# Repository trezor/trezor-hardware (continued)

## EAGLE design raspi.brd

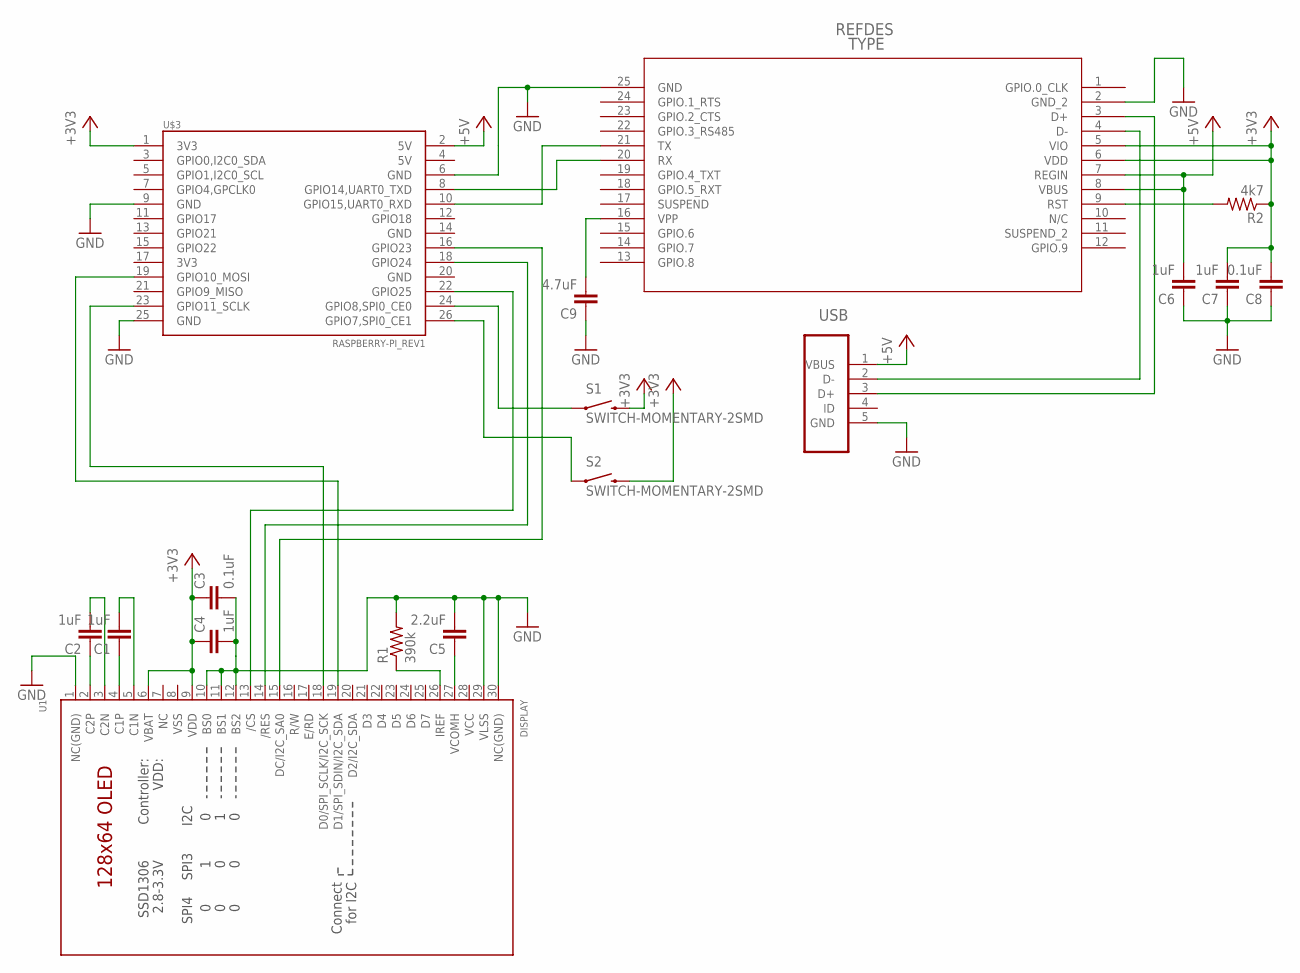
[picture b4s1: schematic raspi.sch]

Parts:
C1, C2, C4, C6, C7: 1uF; 0805
C3, C8: 0.1uF; 0805
C5: 2.2uF; 0805
C9: 4.7uF; 0805
R1: 390k; 0805
R2: 4k7; 0805
S1, S2: SWITCH-MOMENTARY-2SMD; TACTILE_SWITCH_SMD
U1: DISPLAY; UG-2864HSWEG01_0.96IN_WRAPAROUND
U2: CP2110-F01-GM
U$3: RASPBERRY-PI_REV1
USB: 47346-0001; MOLEX_47346-0001

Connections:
+3V3: C3.1, C4.1, C7.2, C8.2, R2.1, S1.3 (2), S2.3 (2), U1.6 (VBAT), U1.9 (VDD), U2.5 (VIO), U2.6 (VDD), U$3.1 (3V3)
+5V: C6.2, U2.7 (REGIN), U2.8 (VBUS), U$3.2 (5V), USB.1 (VBUS)
GND: C3.2, C4.2, C5.2, C6.1, C7.1, C8.1, C9.1, R1.2, U1.1 (NC(GND)), U1.10 (BS0), U1.11 (BS1), U1.12 (BS2), U1.29 (VLSS), U1.30 (NC(GND)), U2.2 (GND_2), U2.25 (GND), U$3.6 (GND), U$3.9 (GND), U$3.25 (GND), USB.5 (GND)
unnamed: U1.19 (D1/SPI_SDIN/I2C_SDA), U$3.19 (GPIO10_MOSI)
unnamed: S2.1, U$3.26 (GPIO7,SPI0_CE1)
unnamed: S1.1, U$3.24 (GPIO8,SPI0_CE0)
unnamed: U1.15 (DC/I2C_SA0), U$3.16 (GPIO23)
unnamed: U1.18 (D0/SPI_SCLK/I2C_SCK), U$3.23 (GPIO11_SCLK)
unnamed: C5.1, U1.27 (VCOMH)
unnamed: U1.13 (/CS), U$3.22 (GPIO25)
unnamed: U1.14 (/RES), U$3.18 (GPIO24)
unnamed: R1.1, U1.26 (IREF)
unnamed: C2.1, U1.2 (C2P)
unnamed: C1.1, U1.4 (C1P)
unnamed: C2.2, U1.3 (C2N)
unnamed: C1.2, U1.5 (C1N)
unnamed: C9.2, U2.16 (VPP)
unnamed: U2.21 (TX), U$3.10 (GPIO15,UART0_RXD)
unnamed: U2.20 (RX), U$3.8 (GPIO14,UART0_TXD)
unnamed: R2.2, U2.9 (RST)
USB_D_N: U2.4 (D-), USB.2 (D-)
USB_D_P: U2.3 (D+), USB.3 (D+)
VCC: U1.28 (VCC)
VSS: U1.8 (VSS)

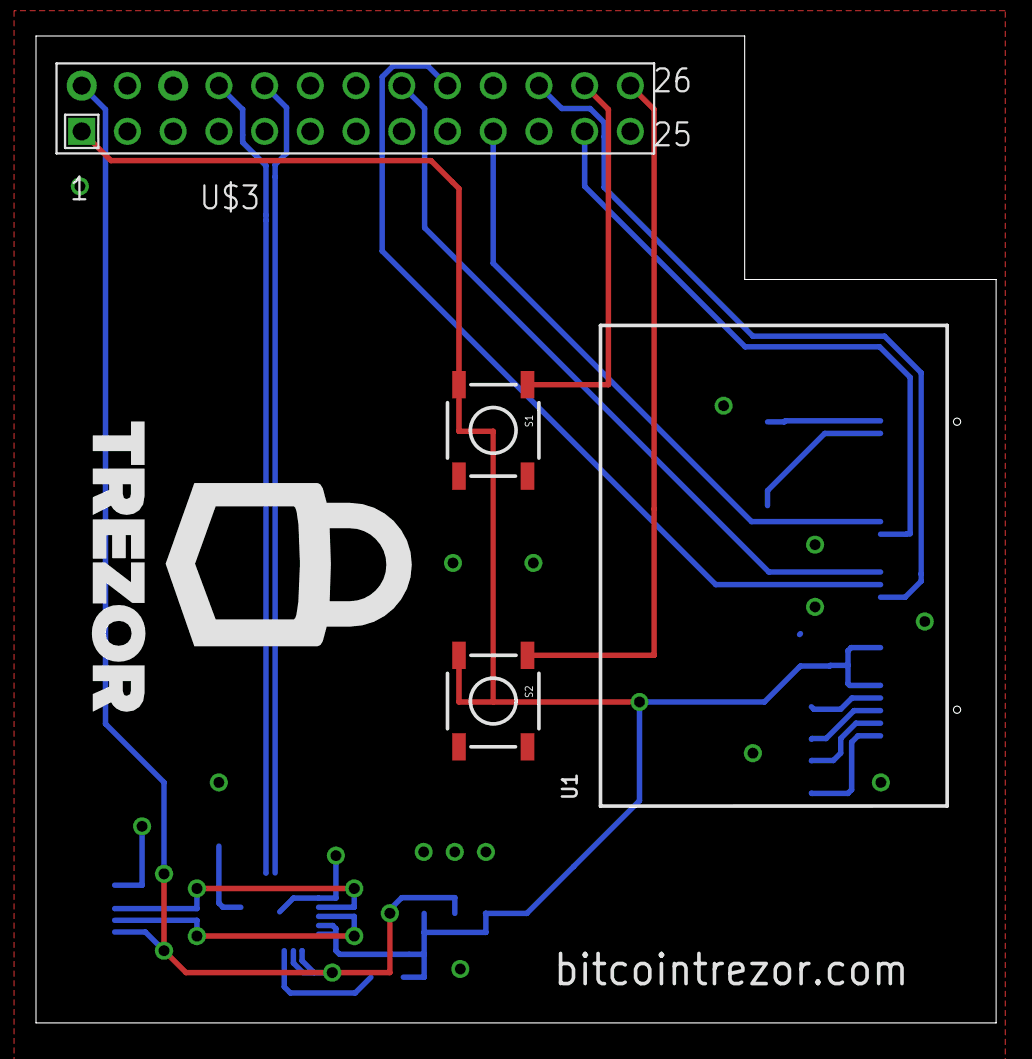
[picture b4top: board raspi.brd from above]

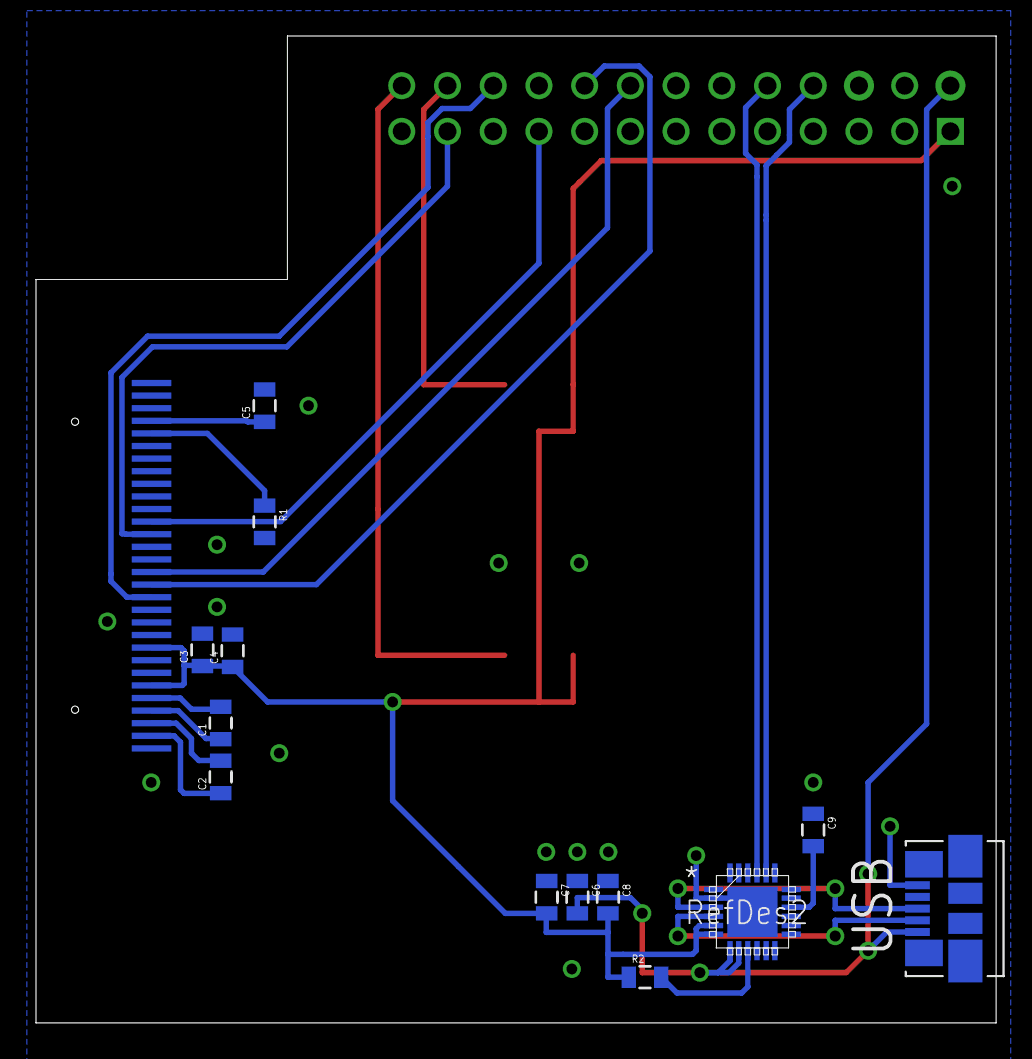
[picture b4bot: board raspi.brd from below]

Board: 2 copper layers, 53.3 x 54.8 mm, 17 parts (13 on the bottom side), 22 nets.

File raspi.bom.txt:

Raspberry shield
================

- 5x SMD 0805 Capacitor 1uF - C1, C2, C4, C6, C7
- 2x SMD 0805 Capacitor 0.1uF - C3, C8
- 1x SMD 0805 Capacitor 2.2uF - C5
- 1x SMD 0805 Capacitor 4.7uF - C9

- 1x SMD 0805 Resistor 390k - R1
- 1x SMD 0805 Resistor 4k7 - R2

- 2x Microbuton P-B17310
  * http://www.gme.cz/mikrospinace-do-dps/p-b17310-p630-143/

- 1x Micro USB (type B) Receptacle Bottom
  * http://cz.farnell.com/molex/47346-0001/micro-usb-type-b-rece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

- 1x SiLabs CP2110 HID-232 converter
  * http://www.silabs.com/products/interface/usbtouart/Pages/usb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

- 1x 2x13 Pinheader
  * http://www.gme.cz/dutinkove-listy/dutinkova-lista-bl826gd-p8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

- 1x OLED display 128x64 UG-2864HSWEG01
  * http://www.wide.hk/products.php?product=128X64-OLED-LED-Disp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

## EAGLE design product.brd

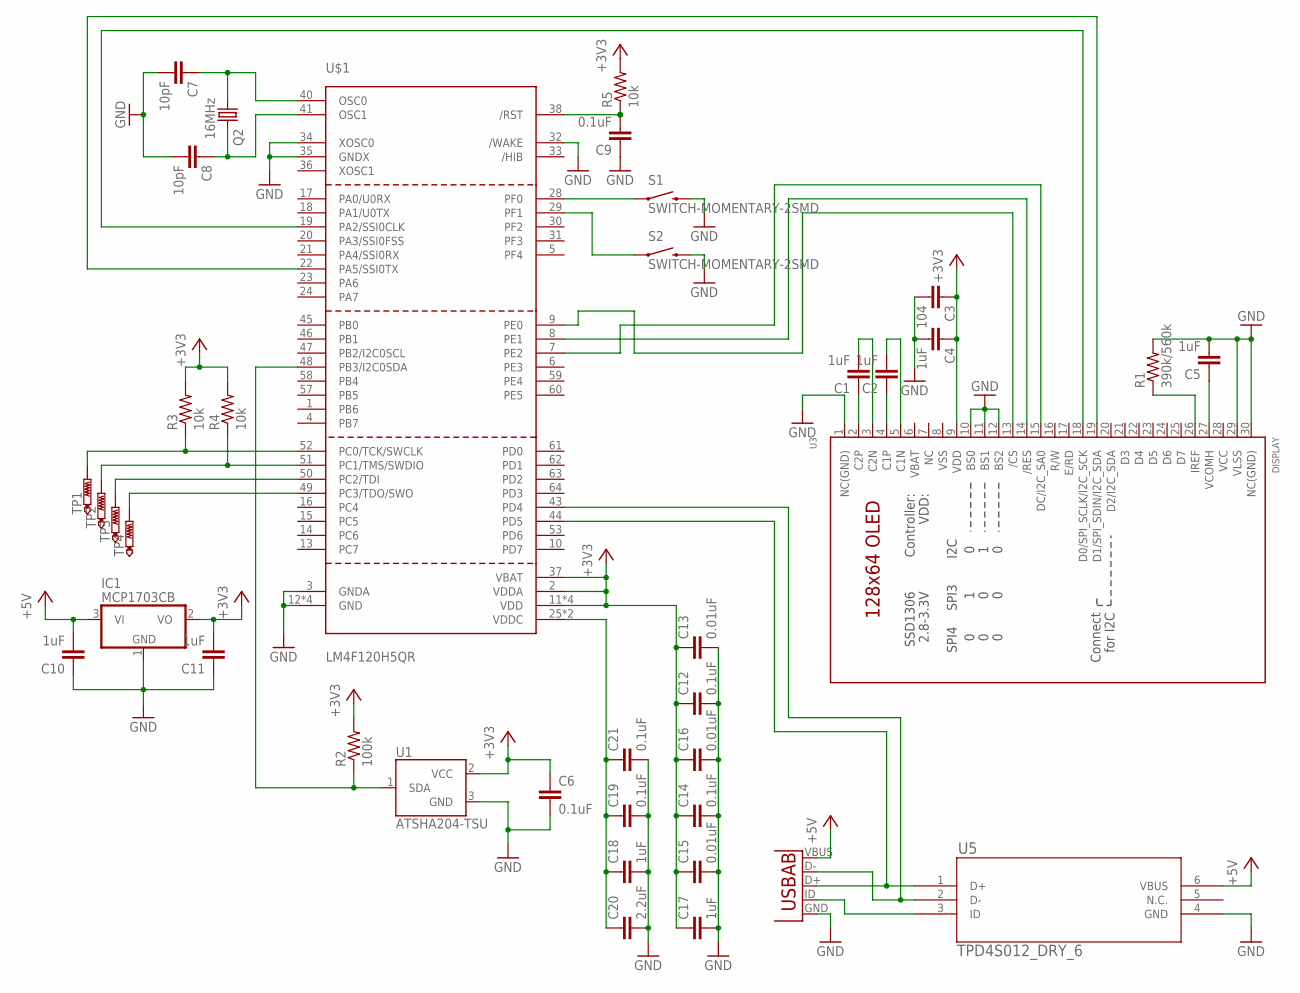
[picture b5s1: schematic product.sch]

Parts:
C1, C2, C4, C5, C10, C11, C17, C18: 1uF; 0402-CAP
C3: 104; 0402-CAP
C6, C9, C12, C14, C19, C21: 0.1uF; 0402-CAP
C7, C8: 10pF; 0402-CAP
C13, C15, C16: 0.01uF; 0402-CAP
C20: 2.2uF; 0402-CAP
IC1: MCP1703CB; SOT23
Q2: 16MHz; CTS406
R1: 390k/560k; 0402-RES
R2: 100k; 0402-RES
R3, R4, R5: 10k; 0402-RES
S1, S2: SWITCH-MOMENTARY-2SMD; TACTILE_SWITCH_SMD
TP1, TP2, TP3, TP4: PTR1TP10R; TP10R
U1: ATSHA204-TSU; SOT23-3
U2: USB; USB-AB-MICRO-SMD
U3: DISPLAY; UG-2864HSWEG01_0.96IN_WRAPAROUND
U5: TPD4S012_DRY_6; DRY6
U$1: LM4F120H5QR; LQFP64

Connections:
+3V3: C3.1, C4.1, C6.1, C11.2, C12.1, C13.1, C14.1, C15.1, C16.1, C17.1, IC1.2 (VO), R2.2, R3.2, R4.2, R5.2, U1.2 (VCC), U3.9 (VDD), U$1.2 (VDDA), U$1.11 (VDD), U$1.26 (VDD), U$1.37 (VBAT), U$1.42 (VDD), U$1.54 (VDD)
+5V: C10.2, IC1.3 (VI), U2.VBUS, U5.6 (VBUS)
GND: C3.2, C4.2, C5.2, C6.2, C7.2, C8.2, C9.1, C10.1, C11.1, C12.2, C13.2, C14.2, C15.2, C16.2, C17.2, C18.2, C19.2, C20.2, C21.2, IC1.1 (GND), R1.2, S1.3 (2), S2.3 (2), U1.3 (GND), U2.GND, U3.1 (NC(GND)), U3.10 (BS0), U3.11 (BS1), U3.12 (BS2), U3.29 (VLSS), U3.30 (NC(GND)), U5.4 (GND), U$1.3 (GNDA), U$1.12 (GND), U$1.27 (GND), U$1.32 (/WAKE), U$1.34 (XOSC0), U$1.35 (GNDX), U$1.39 (GND), U$1.55 (GND)
unnamed: U3.19 (D1/SPI_SDIN/I2C_SDA), U$1.22 (PA5/SSI0TX)
unnamed: U3.13 (/CS), U$1.9 (PE0)
unnamed: U2.ID (USBID), U5.3 (ID)
unnamed: U3.15 (DC/I2C_SA0), U$1.7 (PE2)
unnamed: U3.18 (D0/SPI_SCLK/I2C_SCK), U$1.19 (PA2/SSI0CLK)
unnamed: C5.1, U3.27 (VCOMH)
unnamed: U3.14 (/RES), U$1.8 (PE1)
unnamed: R1.1, U3.26 (IREF)
unnamed: C1.1, U3.2 (C2P)
unnamed: C2.1, U3.4 (C1P)
unnamed: C1.2, U3.3 (C2N)
unnamed: C2.2, U3.5 (C1N)
unnamed: S2.1, U$1.29 (PF1)
unnamed: S1.1, U$1.28 (PF0)
unnamed: R4.1, TP2.TP, U$1.51 (PC1/TMS/SWDIO)
unnamed: R3.1, TP1.TP, U$1.52 (PC0/TCK/SWCLK)
unnamed: TP3.TP, U$1.50 (PC2/TDI)
unnamed: TP4.TP, U$1.49 (PC3/TDO/SWO)
unnamed: C9.2, R5.1, U$1.38 (/RST)
unnamed: C18.1, C19.1, C20.1, C21.1, U$1.25 (VDDC), U$1.56 (VDDC)
SDA: R2.1, U1.1 (SDA), U$1.48 (PB3/I2C0SDA)
USB_D_N: U2.D-, U5.2 (D-), U$1.43 (PD4)
USB_D_P: U2.D+, U5.1 (D+), U$1.44 (PD5)
VCC: U3.28 (VCC)
VSS: U3.8 (VSS)
XTAL1: C7.1, Q2.1, U$1.40 (OSC0)
XTAL2: C8.1, Q2.3 (2), U$1.41 (OSC1)

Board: 2 copper layers, 39 parts (7 on the bottom side), 28 nets, no tracks yet.

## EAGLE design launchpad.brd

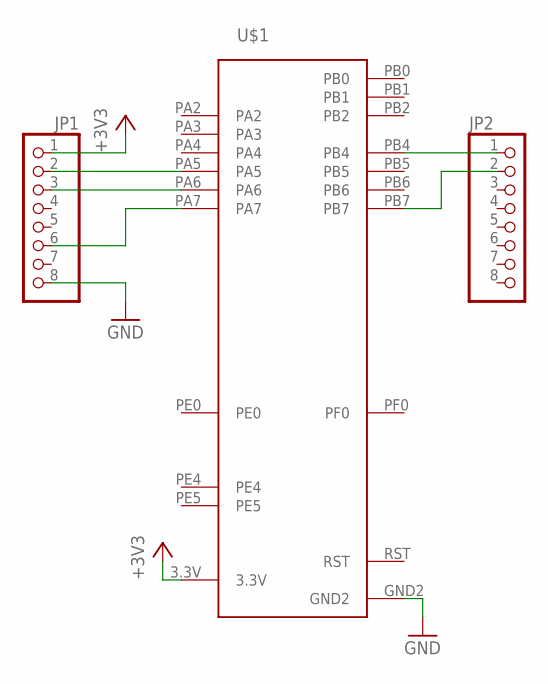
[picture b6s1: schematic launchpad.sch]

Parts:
JP1, JP2: PINHD-1X8; 1X08
U$1: STELLARIS-LAUNCHPAD-COMPATIBLESTELLARIS-LAUNCHPAD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; LAUNCHPAD-COMPATIBLE

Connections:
+3V3: JP1.1, U$1.3.3V
GND: JP1.8, U$1.GND2
unnamed: JP2.2, U$1.PB7
unnamed: JP2.1, U$1.PB4
unnamed: JP1.2, U$1.PA5
unnamed: JP1.3, U$1.PA6
unnamed: JP1.6, U$1.PA7
RST: U$1.RST

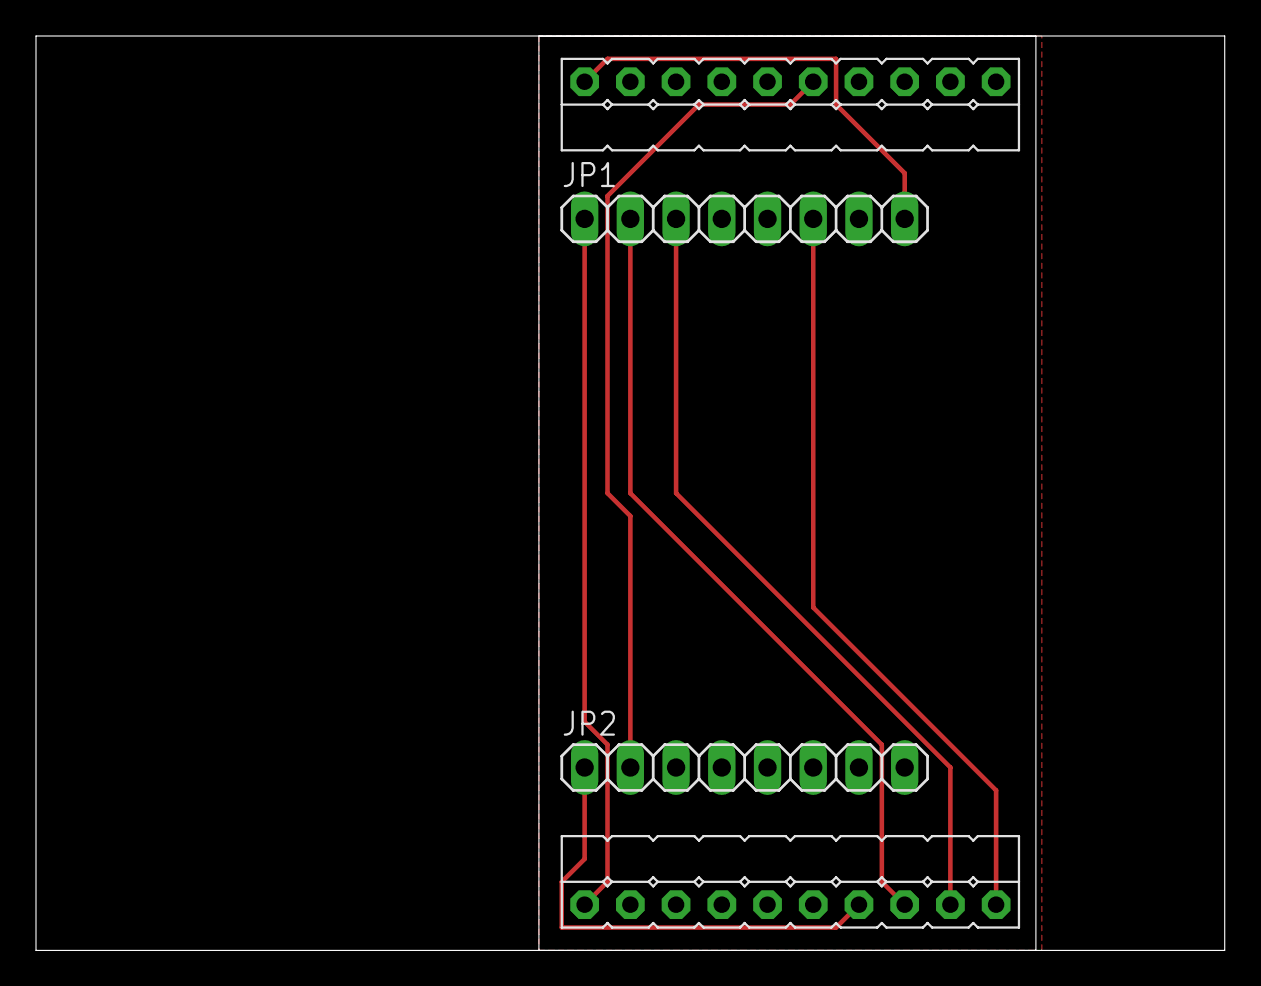
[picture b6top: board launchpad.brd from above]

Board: 2 copper layers, 66.0 x 50.8 mm, 3 parts (0 on the bottom side), 7 nets.

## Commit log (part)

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2012-11-09 init code
2012-11-09 fix distance for display
2012-11-13 rework raspi board
2012-11-13 add gnd polygons
2012-11-13 printing preparations
2012-11-29 add new stls
2013-01-10 work on shield
2013-01-14 work in progress
2013-01-21 work on product scheme
2013-02-03 work on pcbs
2013-02-07 try freerouting
2013-02-07 routed
2013-02-14 new pcb size :-/
2013-02-21 raspi shield
2013-02-21 work on product
2013-02-24 raspi work rename product to trezor
2013-02-25 work snapshot
2013-02-25 forgot to connect usb gnd/vcc
2013-03-09 work on raspi
2013-03-11 work on rpi
2013-03-18 raspi work
2013-03-24 rework BOMs
2013-03-24 logo tDocu->tSilk
2013-03-24 add pinheader
2013-03-25 raspi
2013-04-01 rework to STM32 (WIP)
2013-04-08 trezor WIP
2013-04-08 revert dimension change
2013-04-08 remove unused files
2013-04-08 add url
2013-04-09 move capacitors to the edge
2013-04-12 add items to trezor bom
2013-04-12 fix typo in trezor bom
2013-04-12 align boms
2013-04-15 connect vbus to mcu as well
2013-04-19 programmer
2013-04-24 rework swd programmer
2013-05-02 add farnell links
2013-05-03 fix unconnected pin
2013-06-25 change crystal
2013-07-23 repository cleanup
2014-02-26 add bitmaps
2014-05-28 change capacitor
2015-10-14 add board photo
2015-10-15 cleanup eagle filenames (trezor -> trezor_v1.0, trezor_v1 -> trezor_v1.1)
2016-05-06 add two forgotten missing files about programmer
2016-06-08 STL Models optimized for 3D Printing
2016-10-05 add png export from eagle for programmer and raspi
2017-01-10 -> trezor.io
2017-04-13 use markdown for readme
2017-06-22 add production tools (hidtest)
2017-06-23 production: refactor hidtest
2017-07-18 production: add self-test to test-trezor
2018-01-27 Added BOM for Trezor 1.1
2018-07-04 add license
2020-02-01 Fix issues with 3d printed case
    - Fix mobility of buttons
    - Reinforce lanyard connection
2020-02-01 Fix issues with 3d printed case (#9)
    - Fix mobility of buttons
    - Reinforce lanyard connection
2020-03-12 reorganize "case" folder structure
2020-06-23 Add .circleci/config.yml
2020-09-07 electronics: move Trezor One stuff to subfolder
2020-09-07 electronics: add Trezor Model T resources
2021-02-12 electronics: copy over relevant materials from trezor-firmware repo
2021-02-13 add ZIP link to README
2021-02-13 add kicad files
2021-02-16 Board edge rendering correction on kicad
2021-02-16 Fixed filled zones bug, connection issues
2021-02-16 set PCB width to 1.0 mm
2021-02-16 add CERN-OHL-S license
2021-02-16 add OSHW logo
2021-02-16 kicad import bug fixes
    fixed issues with the usb connector footprint causing kicad to be confused about the correct board edge shape
2021-02-16 add OSHW logo to Trezor One PCB
2021-02-16 add gitignore, remove extraneous kicad files
2021-02-16 remove hidtest
2021-02-16 move gitignore to root
2021-02-24 update mosfet
2021-02-24 remove obsolete T1 board
2021-11-01 add oshwa uid
2023-02-07 update sd-card board link
2023-02-09 update model t bom
2023-11-30 add Trezor Safe 3
2024-07-10 Add Trezor Safe 5 rev F
2025-10-23 Add TS7's electronics hardware designs.
2025-10-27 Slight export overlooks corrected :-)
2026-01-07 Added TS5 rev.G electronic hardware designs.
2026-01-08 Added TS5 rev.G electronic hardware designs
